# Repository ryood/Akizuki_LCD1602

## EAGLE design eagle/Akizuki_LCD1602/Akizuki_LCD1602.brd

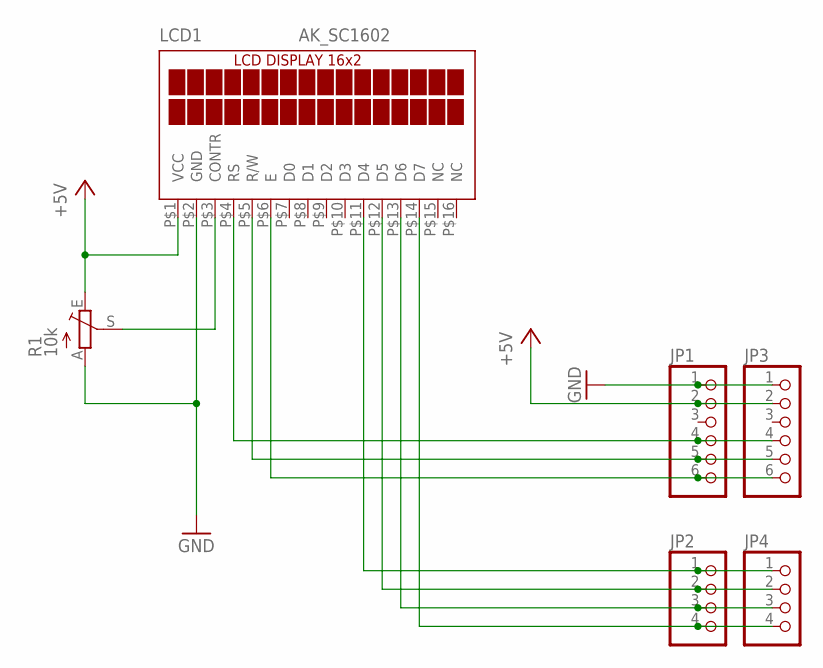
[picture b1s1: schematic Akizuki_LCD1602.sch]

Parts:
JP1, JP3: PINHD-1X6; 1X06
JP2, JP4: PINHD-1X4; 1X04
LCD1: AK_SC1602
R1: 10k; B25P

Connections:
+5V: JP1.2, JP3.2, LCD1.P$1 (VCC), R1.E
GND: JP1.1, JP3.1, LCD1.P$2 (GND), R1.A
unnamed: LCD1.P$3 (CONTR), R1.S
unnamed: JP1.4, JP3.4, LCD1.P$4 (RS)
unnamed: JP1.5, JP3.5, LCD1.P$5 (R/W)
unnamed: JP1.6, JP3.6, LCD1.P$6 (E)
unnamed: JP2.1, JP4.1, LCD1.P$11 (D4)
unnamed: JP2.2, JP4.2, LCD1.P$12 (D5)
unnamed: JP2.3, JP4.3, LCD1.P$13 (D6)
unnamed: JP2.4, JP4.4, LCD1.P$14 (D7)

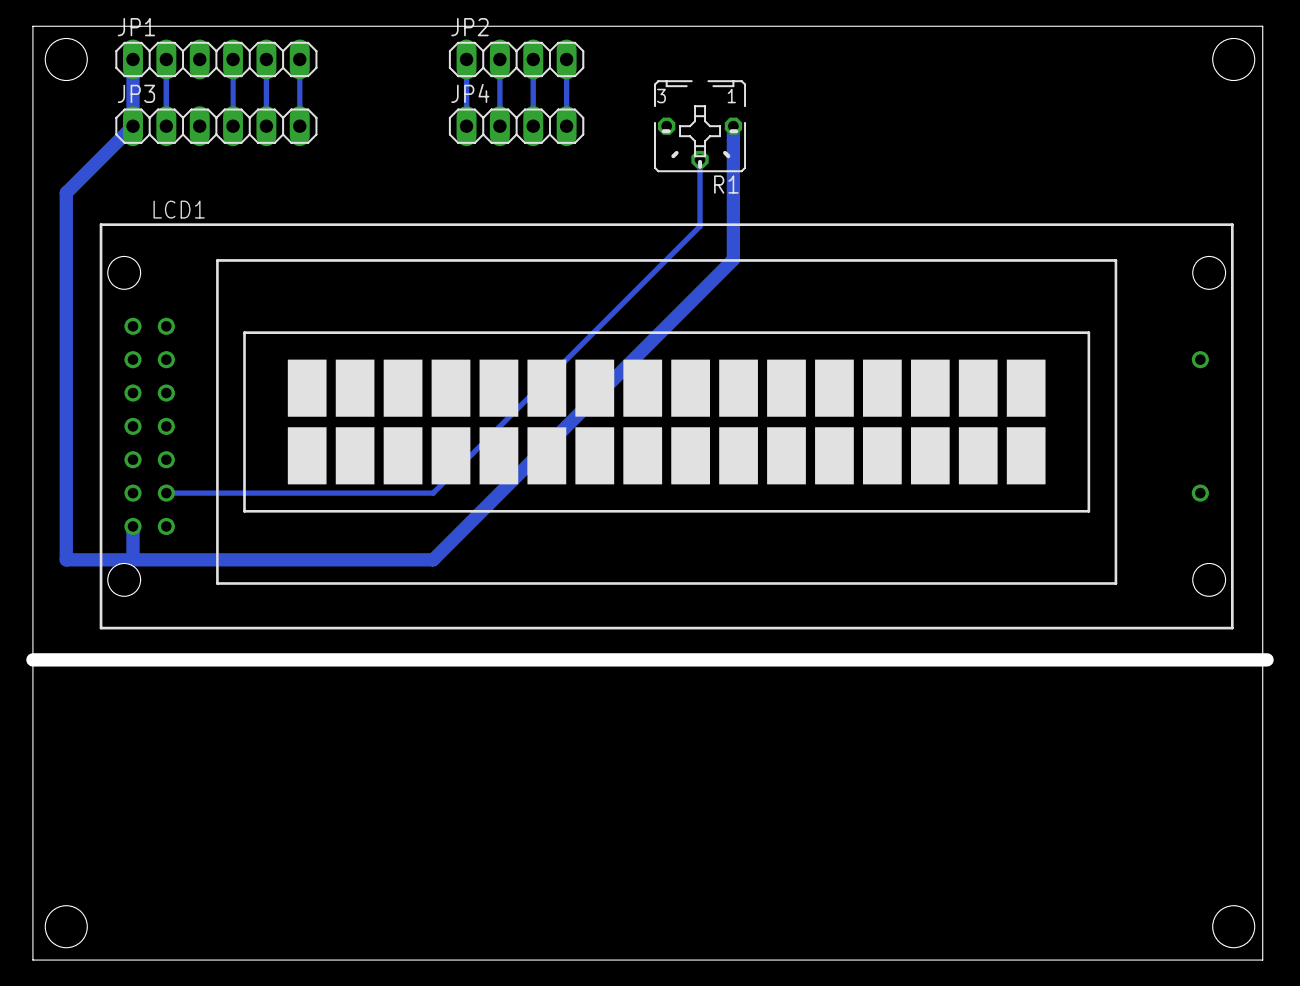
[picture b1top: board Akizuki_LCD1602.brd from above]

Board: 2 copper layers, 94.0 x 70.1 mm, 6 parts (0 on the bottom side), 10 nets.

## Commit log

2017-02-21 ジュンフロン線のジャンパで配線
2017-02-21 Debug
2017-03-01 Add image file
